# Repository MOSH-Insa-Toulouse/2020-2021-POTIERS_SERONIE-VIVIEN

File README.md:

# 2020-2021-POTIERS_SERONIE-VIVIEN

This project is part of the 5ISS year formation at INSA Toulouse.
After designing a nanoparticle gas sensor in the AIME laboratory at INSA Toulouse, we worked on the modeling of the assembly that would allow us to publish its measurements on the campus LoRa gateway.

Tool used : http://kicad-pcb.org/

# KiCad PCB 

The final structure is composed of :

- [x] The gas sensor
- [x] An amplifier stage for home-made gas sensor
- [x] A LoRa RN-2483 microchip for the data transmission
- [x] The Arduino Uno Shield that uses the same pin disposition as Uno board REV 3

# Datasheets of main components

- [x] Datasheet of the LoRa microchip
- [x] Datasheet of the home-made gas sensor
- [x] Datasheet of the Arduino UNO board

# To-Do List 

 - [x] Create KiCad project
 - [x] Design the circuit board
 - [x] Assign the components footprints
 - [x] Design of the pcb
 - [x] Component placement
 - [x] Routing

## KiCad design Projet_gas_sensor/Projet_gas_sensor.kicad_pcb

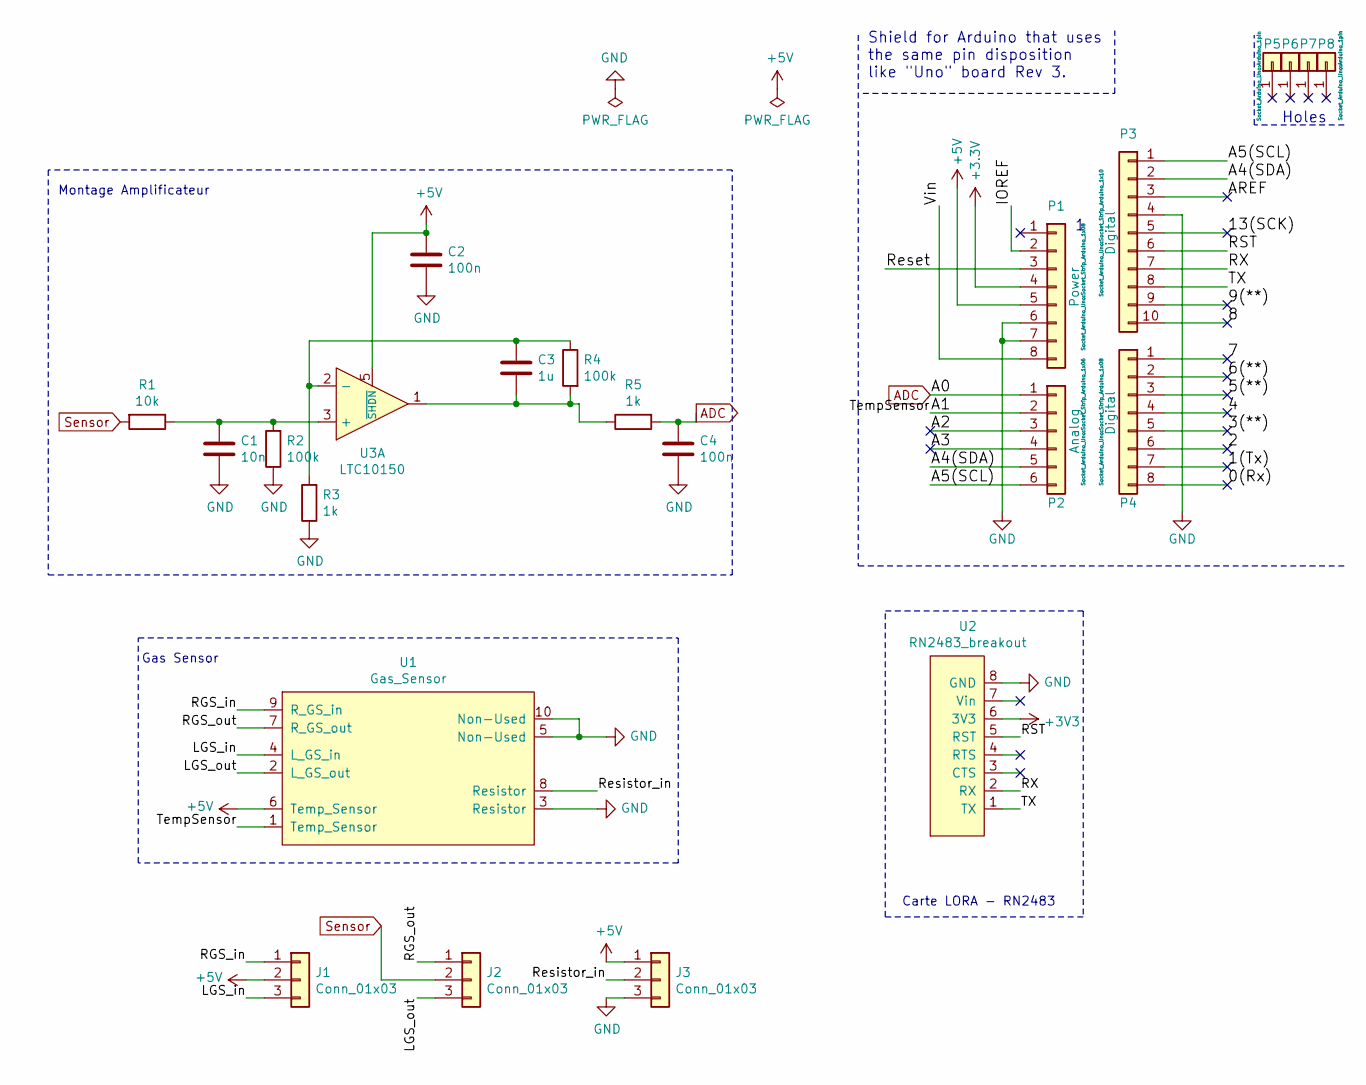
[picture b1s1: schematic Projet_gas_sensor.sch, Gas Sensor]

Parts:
C1: 10n; CP_Elec_3x5.3
C2, C4: 100n; CP_Elec_3x5.3
C3: 1u; CP_Elec_3x5.3
J1, J2, J3: Conn_01x03; PinHeader_1x03_P2.54mm_Vertical
P1: Power; Socket_Strip_Arduino_1x08
P2: Analog; Socket_Strip_Arduino_1x06
P3: Digital; Socket_Strip_Arduino_1x10
P4: Digital; Socket_Strip_Arduino_1x08
P5, P6, P7, P8: CONN_01X01; Arduino_1pin
R1: 10k; R_Axial_DIN0207_L6.3mm_D2.5mm_P7.62mm_Horizontal
R2, R4: 100k; R_Axial_DIN0207_L6.3mm_D2.5mm_P7.62mm_Horizontal
R3, R5: 1k; R_Axial_DIN0207_L6.3mm_D2.5mm_P7.62mm_Horizontal
U1: Gas_Sensor; TO-5-10_Window
U2: RN2483_breakout; LORA
U3: LTC10150; DFN-10-1EP_3x3mm_P0.5mm_EP1.65x2.38mm

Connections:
+5V: C2.1, J1.2, J3.1, P1.5, U1.6 (Temp_Sensor), U3.5 (~SHDN)
/0(Rx): P4.8
/1(Tx): P4.7
/2: P4.6
/3(**): P4.5
/4: P4.4
/5(**): P4.3
/6(**): P4.2
/7: P4.1
/8: P3.10
/9(**): P3.9
/13(SCK): P3.5
/A1: P2.2, U1.1 (Temp_Sensor)
/A2: P2.3
/A3: P2.4
/A4(SDA): P2.5, P3.2
/A5(SCL): P2.6, P3.1
/AREF: P3.3
/IOREF: P1.2
/LGS_in: J1.3, U1.4 (L_GS_in)
/LGS_out: J2.3, U1.2 (L_GS_out)
/RGS_in: J1.1, U1.9 (R_GS_in)
/RGS_out: J2.1, U1.7 (R_GS_out)
/RST: P3.6, U2.5 (RST)
/RX: P3.7, U2.2 (RX)
/Reset: P1.3
/Resistor_in: J3.2, U1.8 (Resistor)
/TX: P3.8, U2.1 (TX)
/Vin: P1.8
ADC: C4.1, P2.1, R5.2
GND: C1.2, C2.2, C4.2, J3.3, P1.6, P1.7, P3.4, R2.1, R3.1, U1.3 (Resistor), U1.5 (Non-Used), U1.10 (Non-Used), U2.8 (GND)
unnamed: C1.1, R1.1, R2.2, U3.3 (+)
unnamed: C3.1, R3.2, R4.1, U3.2 (-)
unnamed: C3.2, R4.2, R5.1, U3.1
Sensor: J2.2, R1.2

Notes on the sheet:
Holes
Shield for Arduino that uses the same pin disposition like "Uno" board Rev 3.
Carte LORA - RN2483
Gas Sensor
Montage Amplificateur

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
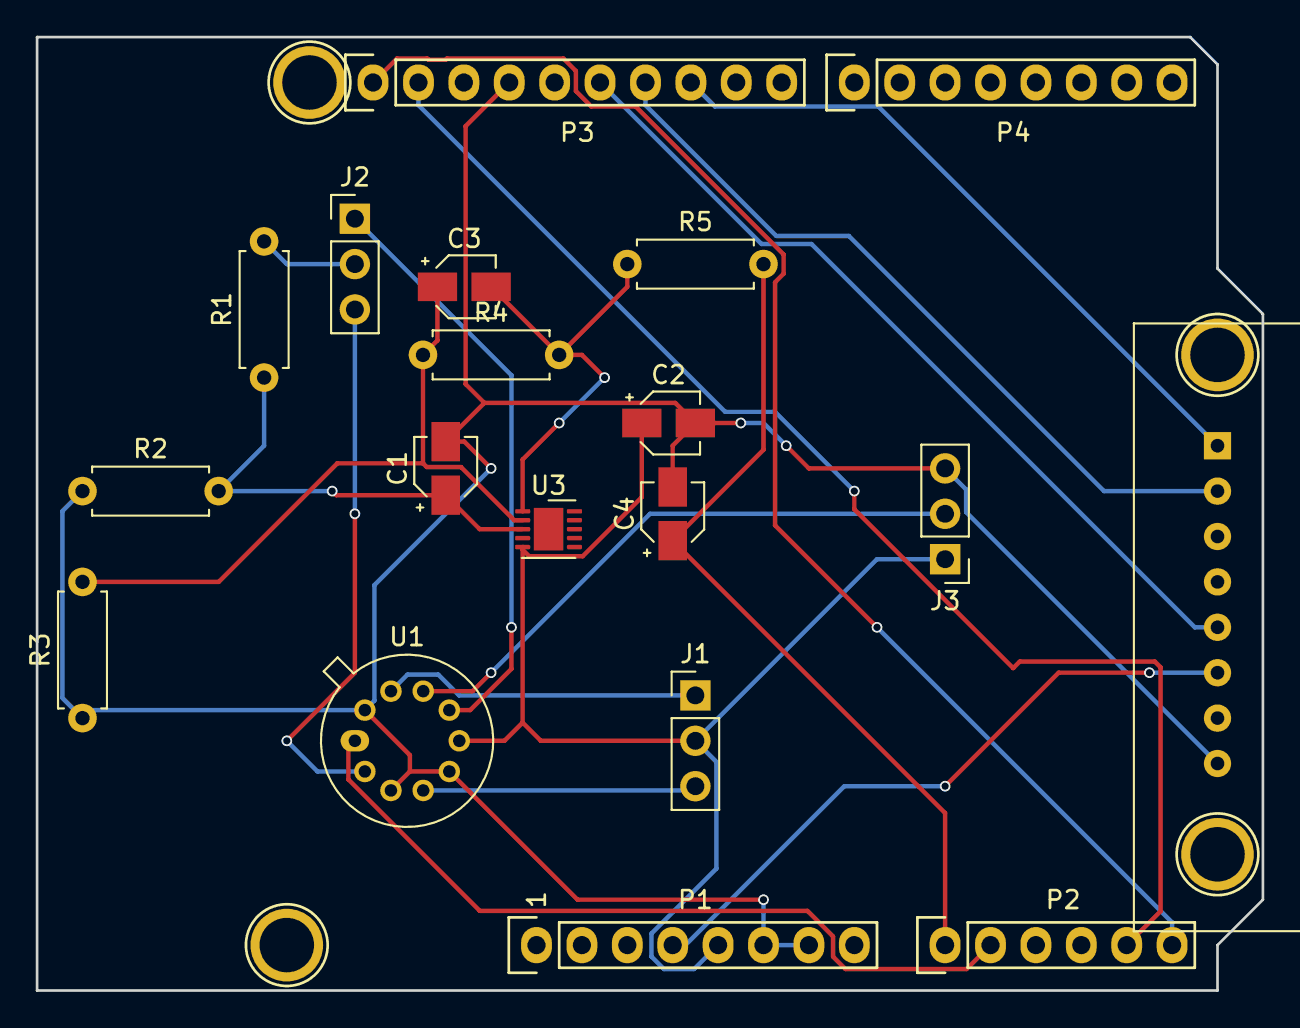
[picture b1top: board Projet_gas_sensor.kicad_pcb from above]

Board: 2 copper layers, 68.6 x 53.3 mm, 23 parts (0 on the bottom side), 19 nets.

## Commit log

2021-01-12 Add files via upload
    Adding RN-2483 Microship datasheet.
2021-01-12 Update README.md
    README-v1
2021-01-12 Update README.md
    README v2
2021-01-12 Add files via upload
    datasheets upload
2021-01-14 Add files via upload
    adding gas sensor datasheet
